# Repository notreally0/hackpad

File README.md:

# Hackpad
My own very little hackpad!

## BOM (Bill of materials)
 - Seeed XIAO RP2040 ×1
 - MX-style mechanical switches ×6
 - Blank DSA keycaps (white) ×6
 - 0.91 inch OLED display (SSD1306, I2C) ×1
 - SK6812 MINI-E RGB LED ×1
 - M3 × 16 mm screws ×4
 - M3 heat-set inserts ×4
 - 3D printed case ×1
## PCB
 <br>
 <br>
 <br>
## CAD
 <br>
 <br>
 <br>
## Firmware
I am using KMK firmware for the hackpad.

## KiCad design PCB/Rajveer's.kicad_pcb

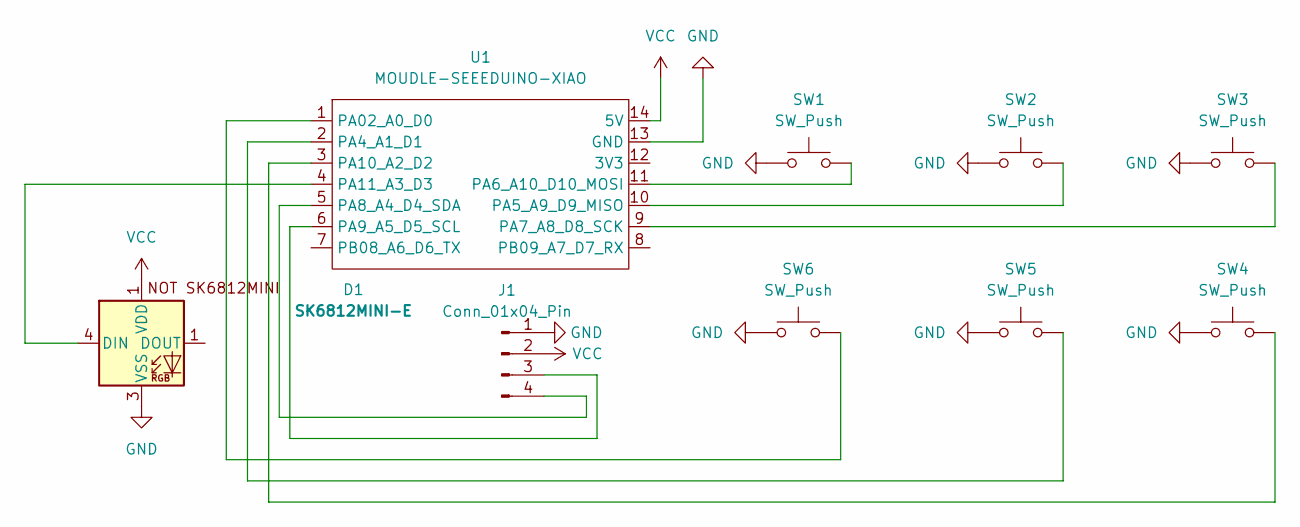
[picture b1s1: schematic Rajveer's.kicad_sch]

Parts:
D1: SK6812MINI-E; SK6812MINI-E_fixed
J1: Conn_01x04_Pin; SSD1306-0.91-OLED-4pin-128x32
SW1, SW2, SW3, SW4, SW5, SW6: SW_Push; SW_Cherry_MX_1.00u_PCB
U1: MOUDLE-SEEEDUINO-XIAO; XIAO-Generic-Hybrid-14P-2.54-21X17.8MM

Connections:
GND: D1.3 (VSS), J1.1, SW1.1, SW2.1, SW3.1, SW4.1, SW5.1, SW6.1, U1.13 (GND)
unnamed: D1.4 (DIN), U1.4 (PA11_A3_D3)
unnamed: J1.3, U1.6 (PA9_A5_D5_SCL)
unnamed: J1.4, U1.5 (PA8_A4_D4_SDA)
unnamed: SW6.2, U1.1 (PA02_A0_D0)
unnamed: SW5.2, U1.2 (PA4_A1_D1)
unnamed: SW2.2, U1.10 (PA5_A9_D9_MISO)
unnamed: SW1.2, U1.11 (PA6_A10_D10_MOSI)
unnamed: SW3.2, U1.9 (PA7_A8_D8_SCK)
unnamed: SW4.2, U1.3 (PA10_A2_D2)
VCC: D1.1 (VDD), J1.2, U1.14 (5V)

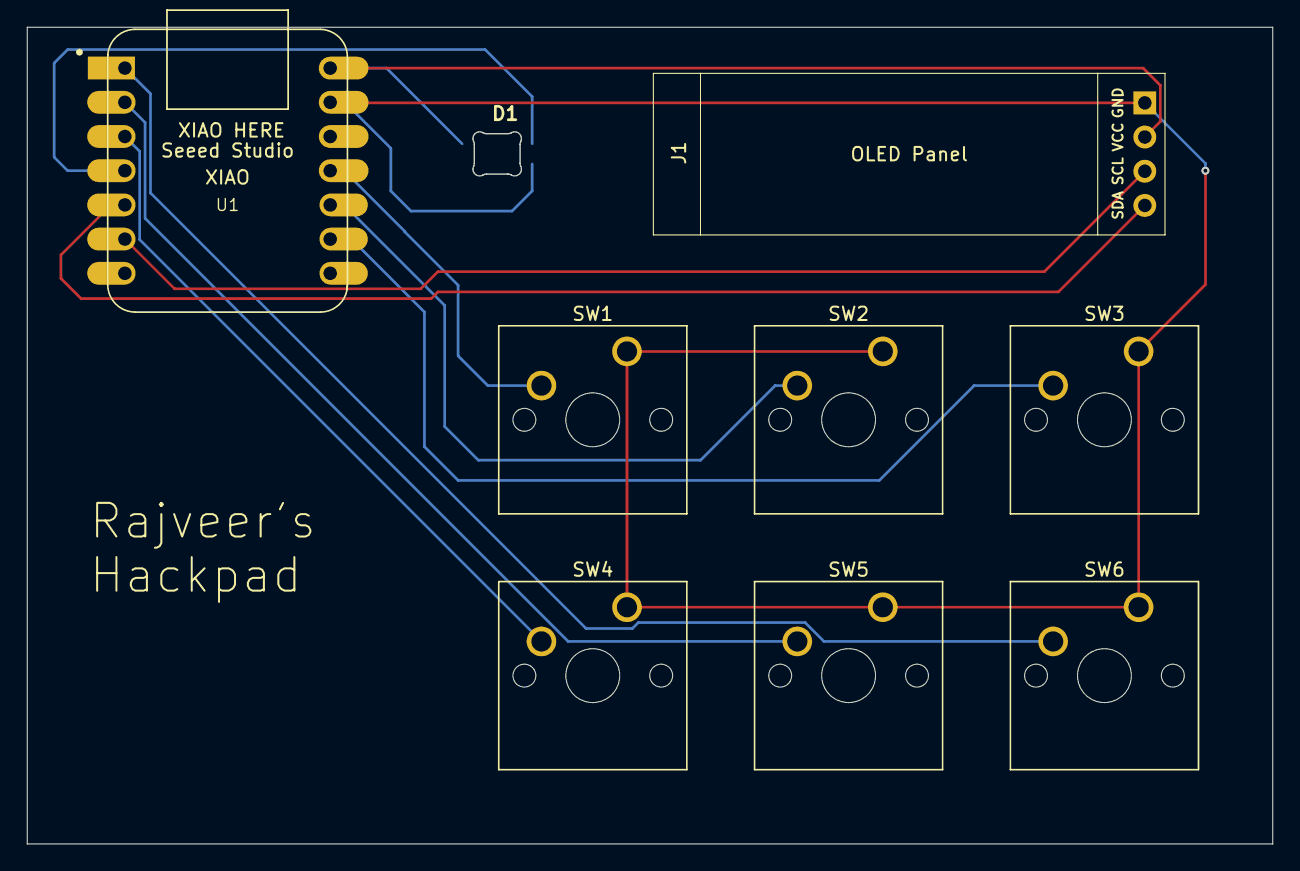
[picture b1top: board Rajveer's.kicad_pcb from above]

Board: 2 copper layers, 92.5 x 60.6 mm, 9 parts (0 on the bottom side), 11 nets.

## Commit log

2025-12-23 Upload all
2025-12-24 Ready for review
